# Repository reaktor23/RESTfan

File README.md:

# RESTfan

A REST controllable wall fan

We bought a cheap wall mount fan which had pull strings for control. Big no no for a Hackerspace :sunglasses:

So we created a small PCB with a 230VAC to 5VDC converter, a Wemos D1 mini and 4 relays on it that allows us to control the fan over a REST API.

# Hardware

We use these components in this project:
 - Fan: [Tristar VE-5874 wall mount ventilator](https://www.tristar.eu/de-de/tristar-ve-5874-wandventilator-ve--5874)
 - AC/DC converter: [HiLink HLK-PM01](http://www.hlktech.net/product_detail.php?ProId=54)
 - Relays: [Finder 30.22](https://www.finder-relais.net/de/finder-relais-serie-30.pdf)
 - ESP8266 Board: [Wemos D1 mini](https://www.wemos.cc/en/latest/d1/d1_mini.html)

# UI

We use [ESPHome](https://esphome.io/) to control the fan as it integrates nicely with [Home Assistant](https://www.home-assistant.io/) which powers our PowerCommander.

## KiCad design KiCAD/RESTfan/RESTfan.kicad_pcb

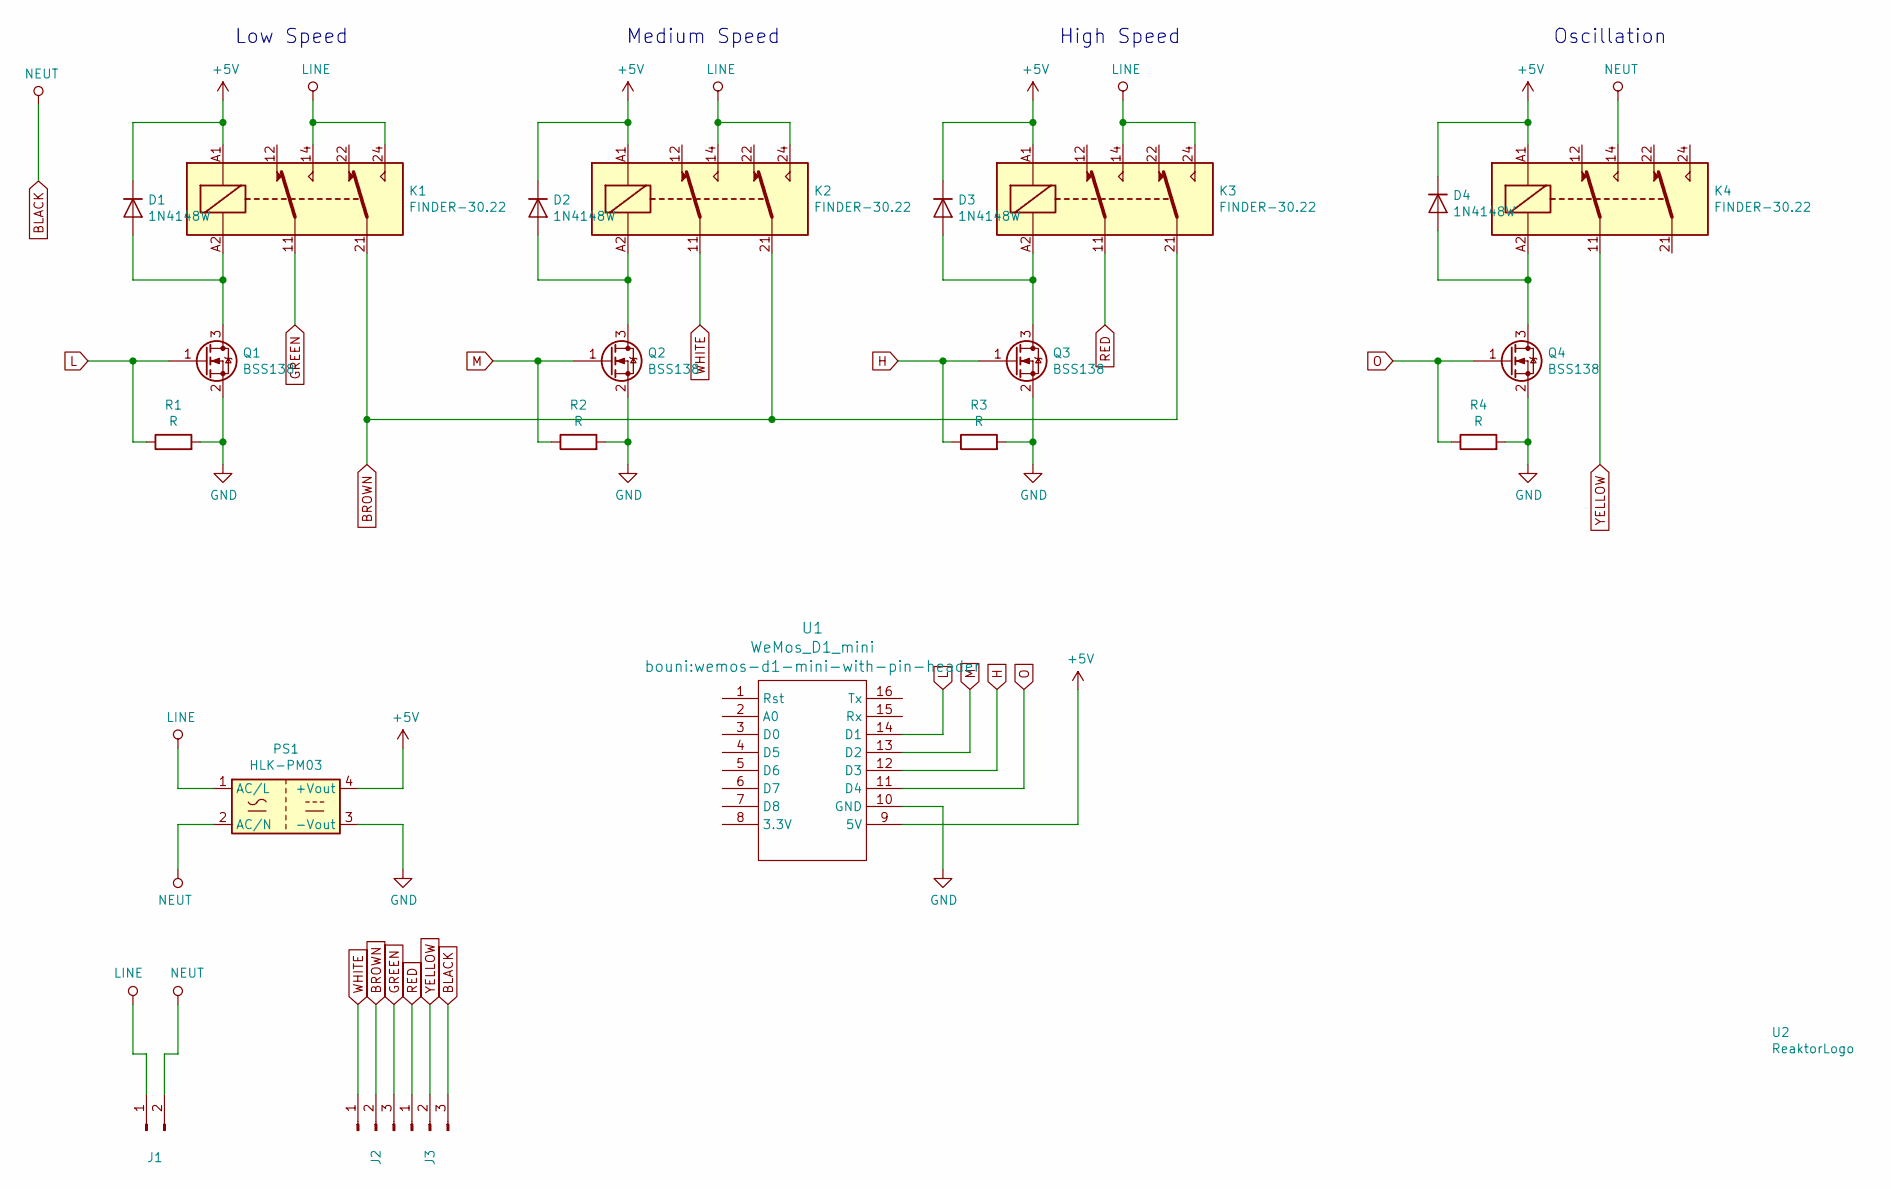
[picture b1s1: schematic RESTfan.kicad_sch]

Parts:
D1, D2, D3, D4: 1N4148W; D_SOD-123
J1: Conn_01x02_Male; SolderWirePad_1x02_P5.08mm_Drill1.5mm
J2, J3: Conn_01x03_Male; SolderWirePad_1x03_P4.445mm_Drill1.5mm
K1, K2, K3, K4: FINDER-30.22; Relay_DPDT_Finder_30.22
PS1: HLK-PM03; Converter_ACDC_HiLink_HLK-PMxx
Q1, Q2, Q3, Q4: BSS138; SOT-23
R1, R2, R3, R4: R; R_0805_2012Metric
U1: WeMos_D1_mini; wemos-d1-mini-with-pin-header
U2: ReaktorLogo; Reaktor23_8mm

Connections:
+5V: D1.1 (K), D2.1 (K), D3.1 (K), D4.1 (K), K1.A1, K2.A1, K3.A1, K4.A1, PS1.4 (+Vout), U1.9 (5V)
BLACK: J1.2, J3.3, K4.14, PS1.2 (AC/N)
BROWN: J2.2, K1.21, K2.21, K3.21
GND: PS1.3 (-Vout), Q1.2 (S), Q2.2 (S), Q3.2 (S), Q4.2 (S), R1.2, R2.2, R3.2, R4.2, U1.10 (GND)
GREEN: J2.3, K1.11
H: Q3.1 (G), R3.1, U1.12 (D3)
L: Q1.1 (G), R1.1, U1.14 (D1)
LINE: J1.1, K1.14, K1.24, K2.14, K2.24, K3.14, K3.24, PS1.1 (AC/L)
M: Q2.1 (G), R2.1, U1.13 (D2)
unnamed: D1.2 (A), K1.A2, Q1.3 (D)
unnamed: D2.2 (A), K2.A2, Q2.3 (D)
unnamed: D3.2 (A), K3.A2, Q3.3 (D)
unnamed: D4.2 (A), K4.A2, Q4.3 (D)
O: Q4.1 (G), R4.1, U1.11 (D4)
RED: J3.1, K3.11
WHITE: J2.1, K2.11
YELLOW: J3.2, K4.11

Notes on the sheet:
Low Speed
Medium Speed
High Speed
Oscillation

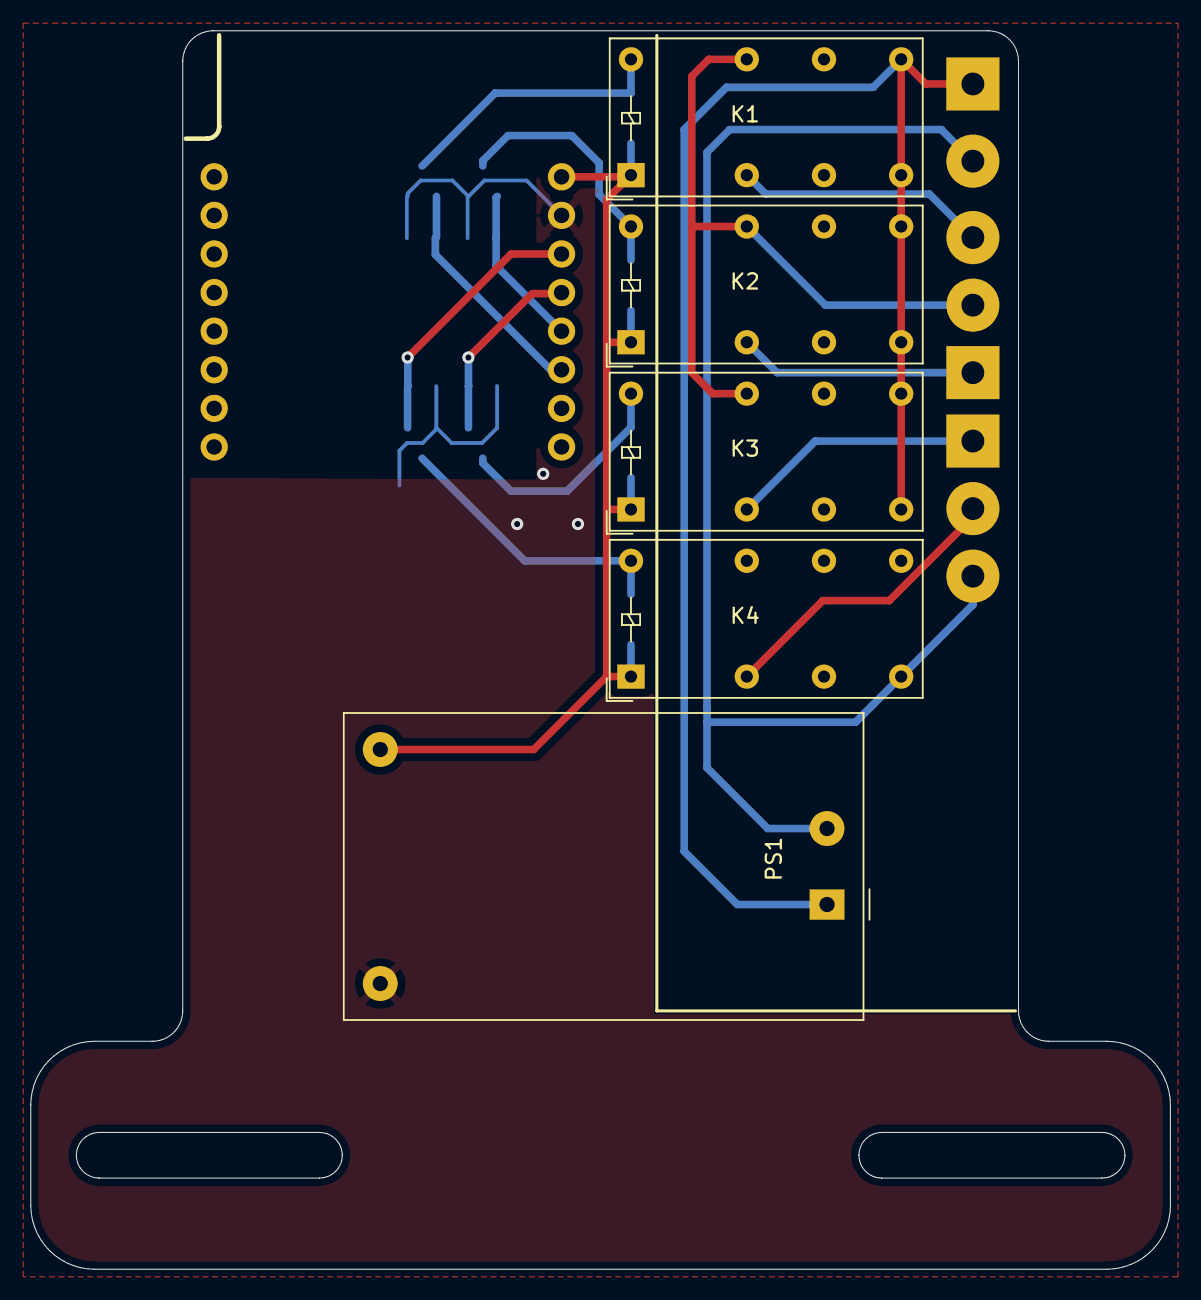
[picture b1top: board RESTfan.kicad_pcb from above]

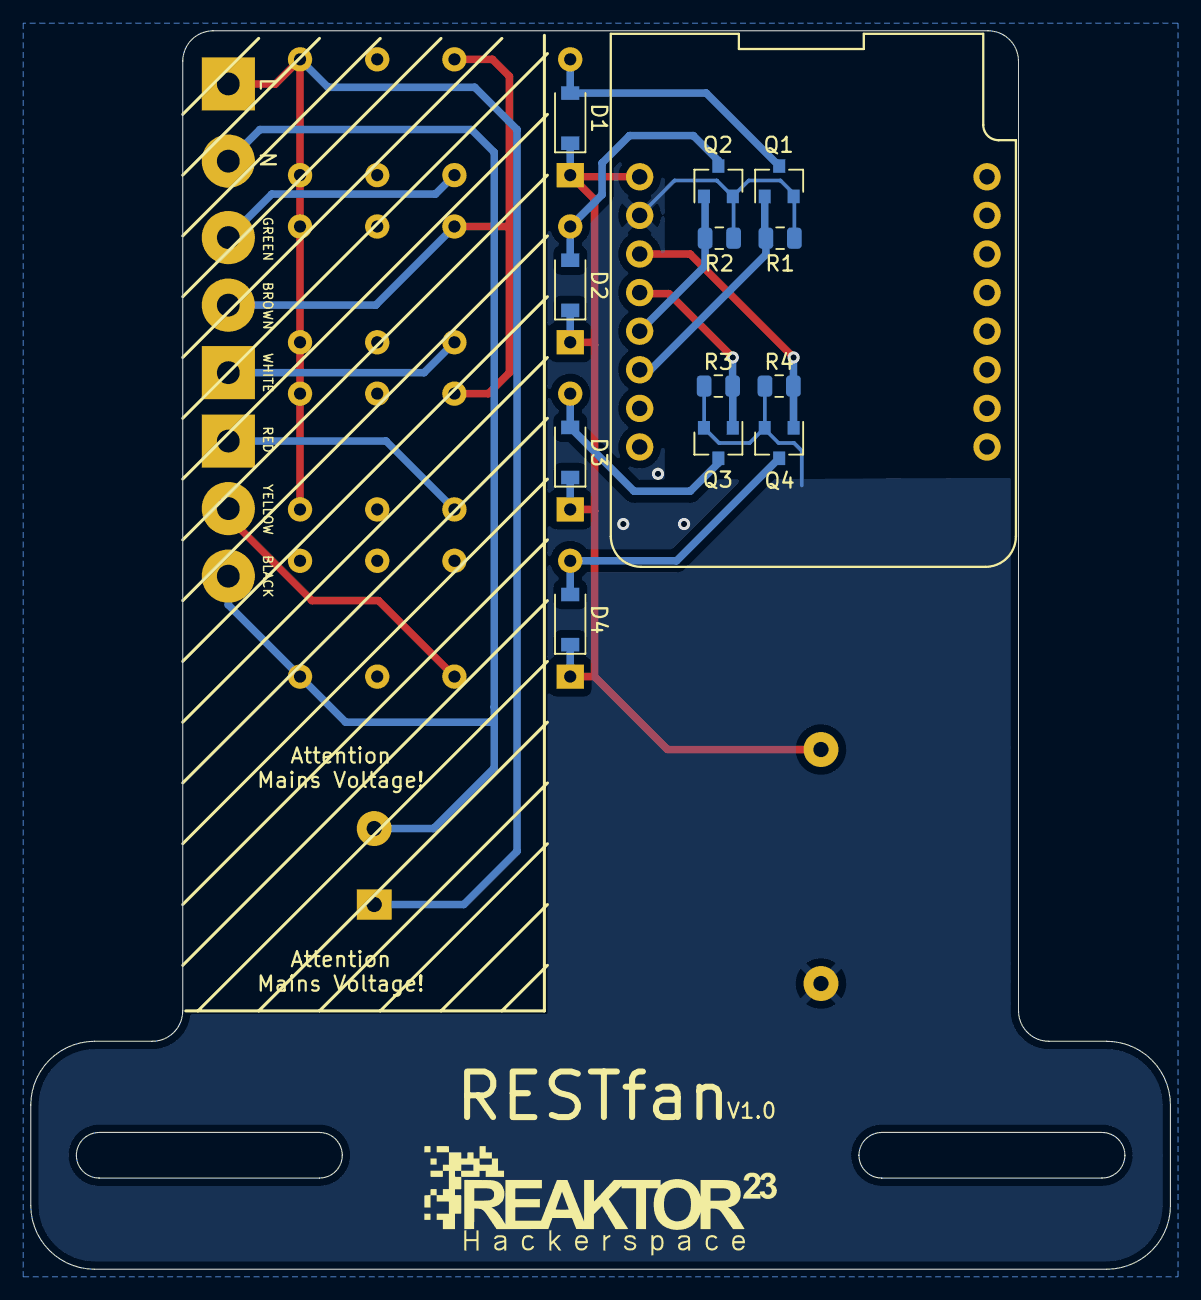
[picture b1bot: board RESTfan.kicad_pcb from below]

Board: 2 copper layers, 75.0 x 81.5 mm, 22 parts (14 on the bottom side), 17 nets.

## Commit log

2020-08-28 fixed typo
2020-09-01 put wifi secrets into seperate .h file, use POST instead of GET
2021-07-26 moved from PlatformIO to ESPhome
2021-07-26 add more documentation
2021-07-26 removed comments, add upper device name
2021-07-26 add secrets.yaml example
